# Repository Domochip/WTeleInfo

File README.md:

# WTeleInfo
Ce projet utilise un D1 mini et quelques composants pour faire remonter les compteurs EDF à votre domotique.

## Construisez votre WTeleInfo

Tous les fichiers necessaires sont dans le sous-dossier schematic et ont été conçu avec KiCAD.

### Schematic

**Spécial Linky** : <u>Il faut remplacer **R2** par une **1.5K** et **C3** n'est **pas necessaire**</u>

### PCB

### Imprimez votre boitier

Le projet du boitier (Fusion 360) se trouve dans le dossier `box` 
(Ainsi que les fichiers STL à imprimer directement) 

### Flash

Le firmware Tasmota-téléinfo est utilisé pour animer le D1Mini  
Vous pouvez le flasher directement depuis la page web "Install tasmota"
https://tasmota.github.io/install/

## Démarrage

### Configuration Tasmota

Vous devez appliquer ce Template :  
`{"NAME":"WTeleInfo","GPIO":[0,0,0,0,0,0,0,0,0,5152,0,0,0,0],"FLAG":0,"BASE":18,"CMND":"Module 0|TelePeriod 60"}`

Commande à executer, si vous possedez un compteur Linky en Mode Standard (nouveau protocole):  
`EnergyConfig Standard`

Pour plus de détails, veuillez vous référer à la documentation officielle :  
https://tasmota.github.io/docs/Teleinfo/

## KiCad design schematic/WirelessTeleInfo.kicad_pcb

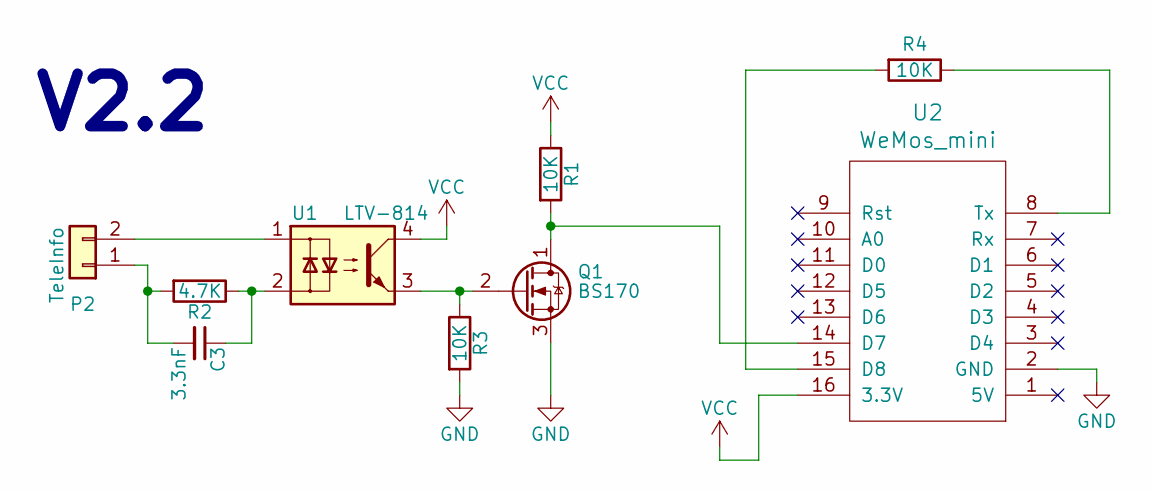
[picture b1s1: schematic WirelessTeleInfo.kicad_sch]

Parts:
C3: 3.3nF; C_0805_HandSoldering
P2: TeleInfo; TerminalBlock_bornier-2_P5.08mm
Q1: BS170; TO-92_Horizontal2_Inline_Narrow_Oval
R1, R3, R4: 10K; R_0805_HandSoldering
R2: 4.7K; R_Axial_DIN0204_L3.6mm_D1.6mm_P2.54mm_Vertical
U1: LTV-814; DIP-4_W7.62mm_Socket_LongPads
U2: WeMos_mini; wemos-d1-mini-DIL-only

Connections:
GND: Q1.3 (S), R3.2, U2.2 (GND)
unnamed: C3.1, R2.1, U1.2
unnamed: C3.2, P2.1, R2.2
unnamed: P2.2, U1.1
unnamed: Q1.1 (D), R1.2, U2.14 (D7)
unnamed: Q1.2 (G), R3.1, U1.3
unnamed: R4.1, U2.8 (Tx)
unnamed: R4.2, U2.15 (D8)
VCC: R1.1, U1.4, U2.16 (3.3V)

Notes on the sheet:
V2.2

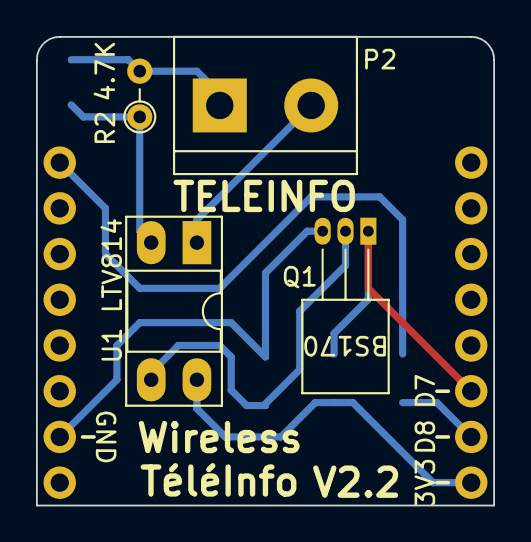
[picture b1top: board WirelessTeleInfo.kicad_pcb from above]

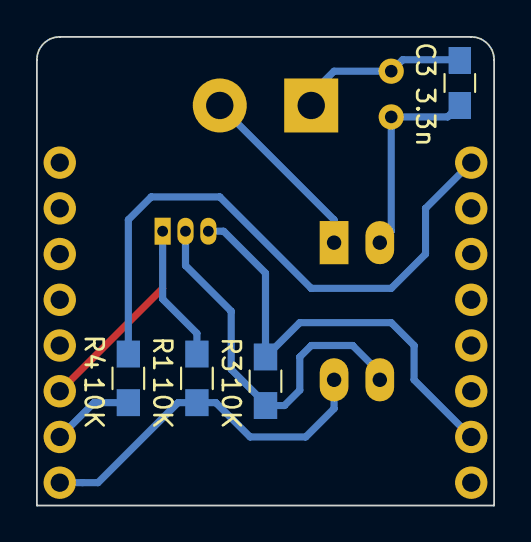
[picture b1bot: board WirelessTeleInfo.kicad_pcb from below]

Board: 2 copper layers, 25.4 x 26.0 mm, 9 parts (5 on the bottom side), 9 nets.

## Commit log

2018-03-13 V3.1.1 Initial Commit
2018-04-03 V3.1.2 Change Data Structure
    Data structure evolved in order to support other Home Automation system
2018-05-26 V3.2.0 Add MQTT + PlatformIO
2018-06-20 Switch to Base V1.0.10
2018-10-26 V1.1.5/3.2.0 Switch to Base V1.1.5
2018-11-17 Switch to Base V1.1.6
    - No More PowerShell
    - GZIP and convertion to header done in python with platformIO
    - Webpages small improvement
2018-11-27 Fix base
2019-01-22 V3.2.1 Add Upload Period
2019-03-17 V3.2.3 Switch to D1 Mini !!! Upgrade to Base V1.1.7
2019-03-17 Switch schematic to D1 Mini
2019-03-17 Change box for D1 Mini (Use Fusion 360)
2019-03-24 V3.2.4 Update to Base V1.2.0 Remove jQuery
2019-03-24 Fix Pure CSS - 1
2019-03-24 Fix Pure CSS - 2
2019-03-27 Update Schematic for better stability
2019-03-27 V3.2.5 use RX2 pin to receive Teleinfo ESPSoftwareSerial removed Add lib dependencies
2019-03-27 Update Box
2019-04-02 Fix RX2 Use
2019-04-05 Fix Schematic
2019-04-05 V3.3.0 TeleInfo Publish Code refactoring Improve MQTT management Use Ticker remove SimpleTimer Update to base V1.2.4
2019-04-05 better feedback of connection
2019-04-06 Add Box in stl format
2019-04-06 Minor Fix and add small log
2019-04-07 PureCSS Fix because of GIT AutoCRLF Windows users enable autocrlf by default, and so pure-min.css crlf modified make bad integrity check
2019-04-07 Fix MQTT Timed Out MQTT gave Timed Out state then no reconnection occured
2019-04-10 Improved copy_base.py
2019-04-10 Improved javascript post function
2019-04-10 Add default MQTT callback
2019-04-10 V3.3.1 BugFix MQTT reconnection
2019-04-22 V3.3.2 No TLS for MQTT Update to Base V1.2.6 Use same WifiClients for MQTT or HTTP
2019-08-12 Update gitignore
2019-10-13 Compatibility with Python3
2019-11-09 Up to Base V1.2.8
2019-11-14 Replace Serial by LOG_SERIAL
2019-11-15 Up to base V1.3.0
2019-11-16 Base fix
2019-11-17 Up to Base V1.3.1
2019-11-18 Change MQTT configuration
2019-11-18 Up to Base V1.3.2
2019-11-22 Up to base V1.3.3
2019-11-22 V3.3.3 Implement EventSource on status
2019-11-23 Naming Convention
2019-11-23 Improve status1.html
2019-11-26 Log AP Name
2019-11-26 small improve on status
2019-11-26 minor fix
2019-11-26 minor improvement
2020-10-16 Update WirelessTeleInfo.cpp
    with latest version of jeedom, completeURI should be now : "http$tls$://$host$/plugins/teleinfo/core/php/jeeTeleinfo.php?apikey=$apikey$&ADCO=$adco$"
2020-11-01 minor clean
2020-11-01 Up to base V1.4.0 /!\ Configuration lost after flash /!\
2021-02-07 Update LibTeleInfo
2021-02-07 Bump Version
2021-02-07 Add PR #18 content from LibTeleinfo
2022-01-25 Up to base V1.4.1
2022-01-26 Add Linky Standard Mode and Update LibTeleInfo
2022-01-26 Jeedom TeleInfo Plugin compatibility
2022-01-26 Looking for Linky SN (ADSC)
2022-01-28 Extend Jeedom apiKey to 64char
2022-01-29 Add Fake Counter to ease debugging
2022-01-29 Fix forbidden + sign in publish topic
2022-01-29 Fix display of values on WebPage
2022-01-29 Prepare use of NewFrame callback
2022-01-29 Add tinfoNewFrame function
2022-01-29 format
2022-01-29 Remove tinfoNewFrame function
2022-01-29 Revert Preparation of NewFrame callback
2022-01-29 Add default MQTT baseTopic
2022-01-30 Better to use placeholder for baseTopic
2022-09-03 remove firmware
2022-09-03 cleanup README.md
2022-09-03 Rename Project
2024-10-18 Cleanup and update schematic to KiCAD 8
2024-10-18 Add gitignore for KiCad
